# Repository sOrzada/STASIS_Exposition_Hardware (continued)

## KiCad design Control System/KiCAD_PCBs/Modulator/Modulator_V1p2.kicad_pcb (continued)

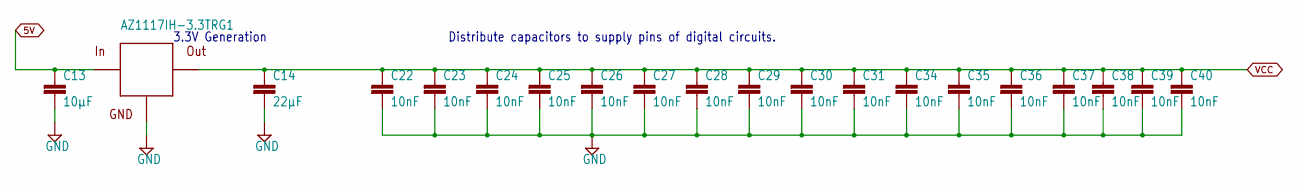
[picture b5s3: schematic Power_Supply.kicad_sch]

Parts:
C13: 10µF; C1206
C14: 22µF; C1206
C22, C23, C24, C25, C26, C27, C28, C29, C30, C31, C34, C35, C36, C37, C38, C39, C40: 10nF; C0603
U$9: AZ1117IH-3.3TRG1; SOT223

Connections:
5V: C13.1, U$9.3 (IN); also elsewhere on the board
GND: C13.2, C14.2, C22.2, C23.2, C24.2, C25.2, C26.2, C27.2, C28.2, C29.2, C30.2, C31.2, C34.2, C35.2, C36.2, C37.2, C38.2, C39.2, C40.2, U$9.1 (GND); also elsewhere on the board
VCC: C14.1, C22.1, C23.1, C24.1, C25.1, C26.1, C27.1, C28.1, C29.1, C30.1, C31.1, C34.1, C35.1, C36.1, C37.1, C38.1, C39.1, C40.1, U$9.2 (OUT), U$9.4 (OUT); also elsewhere on the board

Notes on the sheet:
Distribute capacitors to supply pins of digital circuits.
3.3V Generation

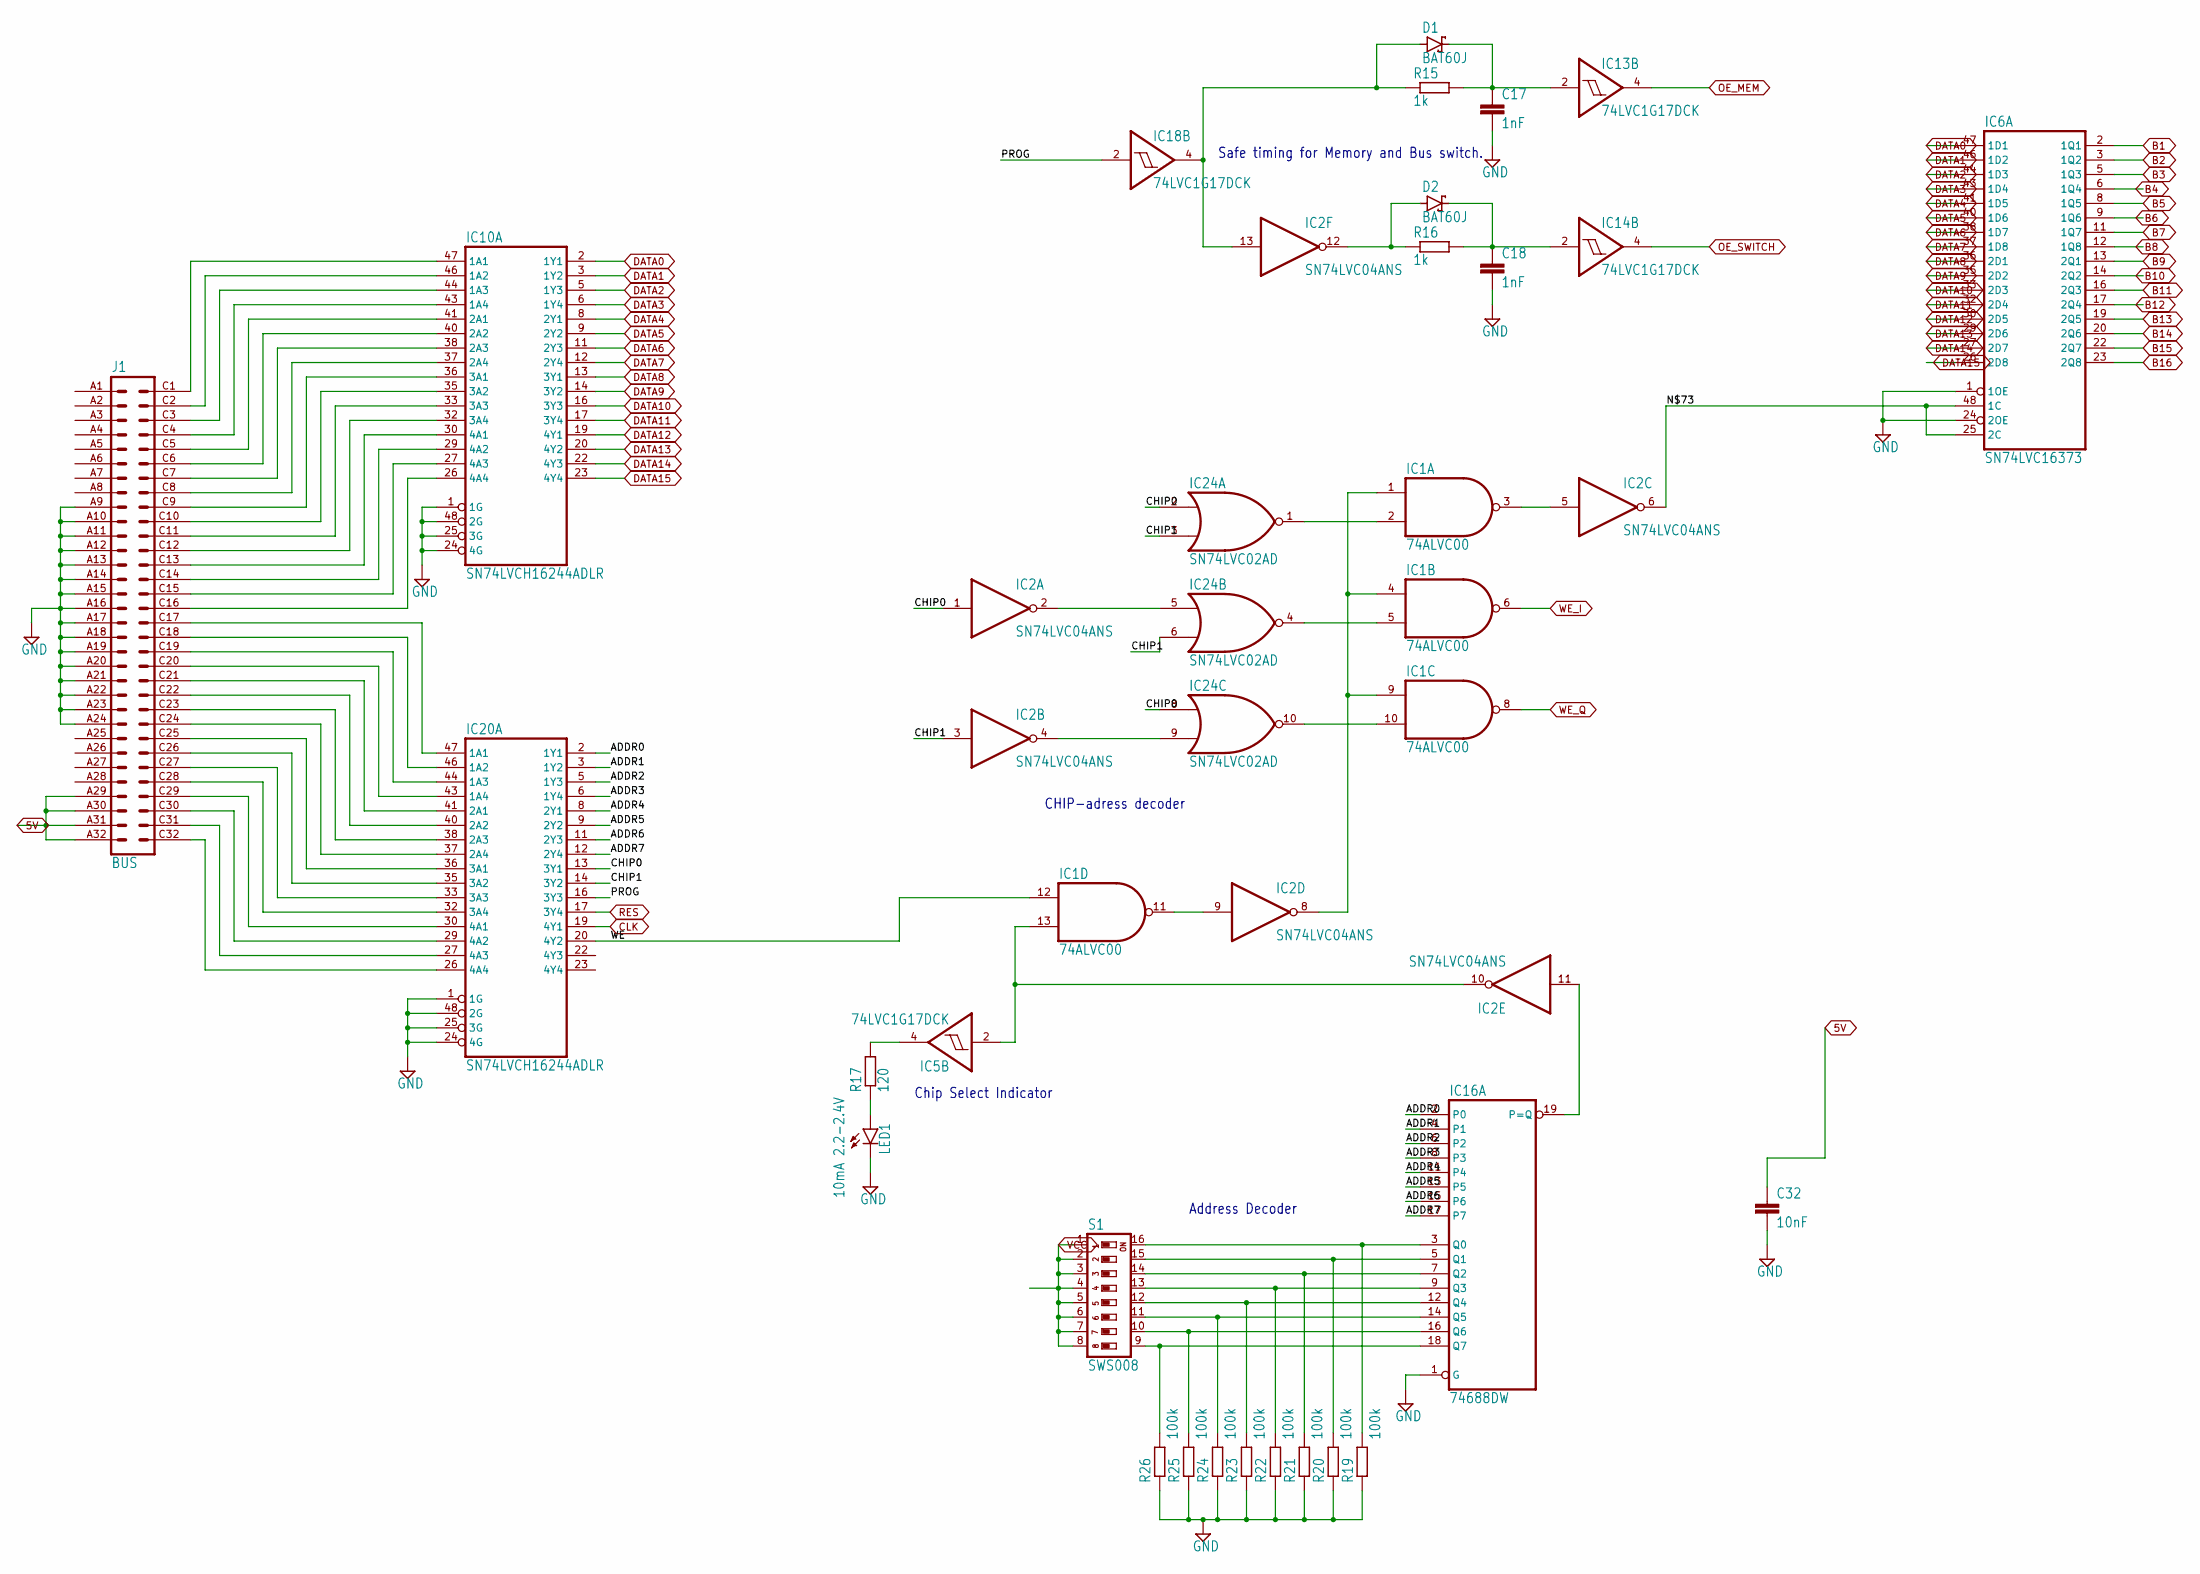
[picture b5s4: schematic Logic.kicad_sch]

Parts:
C17, C18: 1nF; C0805
C32: 10nF; C0603
D1, D2: BAT60J; SOD323_ST
IC1: 74ALVC00; SO14
IC2: SN74LVC04ANS; SO14
IC5, IC13, IC14, IC18: 74LVC1G17DCK; SC70-5
IC6: SN74LVC16373; SSOP48DL
IC10, IC20: SN74LVCH16244ADLR; SSOP48DL
IC16: 74688DW; SO20W
IC24: SN74LVC02AD; SO14
J1: BUS; VG64B
LED1: 10mA 2.2-2.4V; LED3MM
R15, R16: 1k; R0603
R17: 120; R0603
R19, R20, R21, R22, R23, R24, R25, R26: 100k; R0603
S1: SWS008; SMS-008

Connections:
5V: C32.1, J1.A29, J1.A30, J1.A31, J1.A32; also elsewhere on the board
ADDR0: IC16.2 (P0), IC20.2 (1Y1)
ADDR1: IC16.4 (P1), IC20.3 (1Y2)
ADDR2: IC16.6 (P2), IC20.5 (1Y3)
ADDR3: IC16.8 (P3), IC20.6 (1Y4)
ADDR4: IC16.11 (P4), IC20.8 (2Y1)
ADDR5: IC16.13 (P5), IC20.9 (2Y2)
ADDR6: IC16.15 (P6), IC20.11 (2Y3)
ADDR7: IC16.17 (P7), IC20.12 (2Y4)
B1: IC6.2 (1Q1); also elsewhere on the board
B2: IC6.3 (1Q2); also elsewhere on the board
B3: IC6.5 (1Q3); also elsewhere on the board
B4: IC6.6 (1Q4); also elsewhere on the board
B5: IC6.8 (1Q5); also elsewhere on the board
B6: IC6.9 (1Q6); also elsewhere on the board
B7: IC6.11 (1Q7); also elsewhere on the board
B8: IC6.12 (1Q8); also elsewhere on the board
B9: IC6.13 (2Q1); also elsewhere on the board
B10: IC6.14 (2Q2); also elsewhere on the board
B11: IC6.16 (2Q3); also elsewhere on the board
B12: IC6.17 (2Q4); also elsewhere on the board
B13: IC6.19 (2Q5); also elsewhere on the board
B14: IC6.20 (2Q6); also elsewhere on the board
B15: IC6.22 (2Q7); also elsewhere on the board
B16: IC6.23 (2Q8); also elsewhere on the board
CHIP0: IC2.1 (I), IC20.13 (3Y1), IC24.2 (I0), IC24.8 (I0)
CHIP1: IC2.3 (I), IC20.14 (3Y2), IC24.3 (I1), IC24.6 (I1)
CLK: IC20.19 (4Y1); also elsewhere on the board
DATA0: IC6.47 (1D1), IC10.2 (1Y1); also elsewhere on the board
DATA1: IC6.46 (1D2), IC10.3 (1Y2); also elsewhere on the board
DATA2: IC6.44 (1D3), IC10.5 (1Y3); also elsewhere on the board
DATA3: IC6.43 (1D4), IC10.6 (1Y4); also elsewhere on the board
DATA4: IC6.41 (1D5), IC10.8 (2Y1); also elsewhere on the board
DATA5: IC6.40 (1D6), IC10.9 (2Y2); also elsewhere on the board
DATA6: IC6.38 (1D7), IC10.11 (2Y3); also elsewhere on the board
DATA7: IC6.37 (1D8), IC10.12 (2Y4); also elsewhere on the board
DATA8: IC6.36 (2D1), IC10.13 (3Y1); also elsewhere on the board
DATA9: IC6.35 (2D2), IC10.14 (3Y2); also elsewhere on the board
DATA10: IC6.33 (2D3), IC10.16 (3Y3); also elsewhere on the board
DATA11: IC6.32 (2D4), IC10.17 (3Y4); also elsewhere on the board
DATA12: IC6.30 (2D5), IC10.19 (4Y1); also elsewhere on the board
DATA13: IC6.29 (2D6), IC10.20 (4Y2); also elsewhere on the board
DATA14: IC6.27 (2D7), IC10.22 (4Y3); also elsewhere on the board
DATA15: IC6.26 (2D8), IC10.23 (4Y4); also elsewhere on the board
GND: C17.2, C18.2, C32.2, IC1.7 (GND), IC2.7 (GND), IC5.3 (GND), IC6.1 (1OE), IC6.4 (GND@1), IC6.10 (GND@2), IC6.15 (GND@3), IC6.21 (GND@4), IC6.24 (2OE), IC6.28 (GND@5), IC6.34 (GND@6), IC6.39 (GND@7), IC6.45 (GND@8), IC10.1 (1G), IC10.4 (GND@1), IC10.10 (GND@2), IC10.15 (GND@3), IC10.21 (GND@4), IC10.24 (4G), IC10.25 (3G), IC10.28 (GND@5), IC10.34 (GND@6), IC10.39 (GND@7), IC10.45 (GND@8), IC10.48 (2G), IC13.3 (GND), IC14.3 (GND), IC16.1 (G), IC16.10 (GND), IC18.3 (GND), IC20.1 (1G), IC20.4 (GND@1), IC20.10 (GND@2), IC20.15 (GND@3), IC20.21 (GND@4), IC20.24 (4G), IC20.25 (3G), IC20.28 (GND@5), IC20.34 (GND@6), IC20.39 (GND@7), IC20.45 (GND@8), IC20.48 (2G), IC24.7 (GND), J1.A9, J1.A10, J1.A11, J1.A12, J1.A13, J1.A14, J1.A15, J1.A16, J1.A17, J1.A18, J1.A19, J1.A20, J1.A21, J1.A22, J1.A23, J1.A24, LED1.K (C), R19.1, R20.1, R21.1, R22.1, R23.1, R24.1, R25.1, R26.1; also elsewhere on the board
unnamed: IC10.47 (1A1), J1.C1
unnamed: IC10.46 (1A2), J1.C2
unnamed: C17.1, D1.C, IC13.2 (I), R15.2
unnamed: IC10.44 (1A3), J1.C3
unnamed: IC10.43 (1A4), J1.C4
unnamed: IC10.41 (2A1), J1.C5
unnamed: IC10.40 (2A2), J1.C6
unnamed: IC10.38 (2A3), J1.C7
unnamed: IC10.37 (2A4), J1.C8
unnamed: IC10.36 (3A1), J1.C9
unnamed: IC10.35 (3A2), J1.C10
unnamed: IC10.33 (3A3), J1.C11
unnamed: IC10.32 (3A4), J1.C12
unnamed: IC10.30 (4A1), J1.C13
unnamed: IC10.29 (4A2), J1.C14
unnamed: IC10.27 (4A3), J1.C15
unnamed: IC10.26 (4A4), J1.C16
unnamed: IC20.47 (1A1), J1.C17
unnamed: IC20.46 (1A2), J1.C18
unnamed: IC20.44 (1A3), J1.C19
unnamed: IC20.43 (1A4), J1.C20
unnamed: IC20.41 (2A1), J1.C21
unnamed: IC20.40 (2A2), J1.C22
unnamed: IC20.38 (2A3), J1.C23
unnamed: IC20.37 (2A4), J1.C24
unnamed: IC20.36 (3A1), J1.C25
unnamed: IC20.35 (3A2), J1.C26
unnamed: IC20.33 (3A3), J1.C27
unnamed: IC16.3 (Q0), R19.2, S1.16
unnamed: C18.1, D2.C, IC14.2 (I), R16.2
unnamed: D2.A, IC2.12 (O), R16.1
unnamed: IC16.5 (Q1), R20.2, S1.15
unnamed: IC16.7 (Q2), R21.2, S1.14
unnamed: IC16.9 (Q3), R22.2, S1.13
unnamed: IC16.12 (Q4), R23.2, S1.12
unnamed: IC16.14 (Q5), R24.2, S1.11
unnamed: IC16.16 (Q6), R25.2, S1.10
unnamed: IC16.18 (Q7), R26.2, S1.9
unnamed: IC1.2 (I1), IC24.1 (O)
unnamed: IC1.5 (I1), IC24.4 (O)
unnamed: IC2.6 (O), IC6.25 (2C), IC6.48 (1C)
unnamed: D1.A, IC2.13 (I), IC18.4 (O), R15.1
unnamed: IC2.2 (O), IC24.5 (I0)
unnamed: IC2.4 (O), IC24.9 (I1)
unnamed: IC20.32 (3A4), J1.C28
unnamed: IC1.10 (I1), IC24.10 (O)
unnamed: IC1.3 (O), IC2.5 (I)
unnamed: IC2.11 (I), IC16.19 (P=Q)
unnamed: IC1.13 (I1), IC2.10 (O), IC5.2 (I)
unnamed: IC1.1 (I0), IC1.4 (I0), IC1.9 (I0), IC2.8 (O)
unnamed: IC1.11 (O), IC2.9 (I)
unnamed: IC20.30 (4A1), J1.C29
unnamed: IC20.29 (4A2), J1.C30
unnamed: IC20.27 (4A3), J1.C31
unnamed: IC20.26 (4A4), J1.C32
unnamed: LED1.A, R17.1
unnamed: IC5.4 (O), R17.2
OE_MEM: IC13.4 (O); also elsewhere on the board
OE_SWITCH: IC14.4 (O); also elsewhere on the board
PROG: IC18.2 (I), IC20.16 (3Y3)
RES: IC20.17 (3Y4); also elsewhere on the board
VCC: IC1.14 (VCC), IC2.14 (VCC), IC5.5 (VCC), IC6.7 (VCC@1), IC6.18 (VCC@2), IC6.31 (VCC@3), IC6.42 (VCC@4), IC10.7 (VCC@1), IC10.18 (VCC@2), IC10.31 (VCC@3), IC10.42 (VCC@4), IC13.5 (VCC), IC14.5 (VCC), IC16.20 (VCC), IC18.5 (VCC), IC20.7 (VCC@1), IC20.18 (VCC@2), IC20.31 (VCC@3), IC20.42 (VCC@4), IC24.14 (VCC), S1.1, S1.2, S1.3, S1.4, S1.5, S1.6, S1.7, S1.8; also elsewhere on the board
WE: IC1.12 (I0), IC20.20 (4Y2)
WE_I: IC1.6 (O); also elsewhere on the board
WE_Q: IC1.8 (O); also elsewhere on the board

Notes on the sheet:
Address Decoder
Chip Select Indicator
Safe timing for Memory and Bus switch.
CHIP-adress decoder

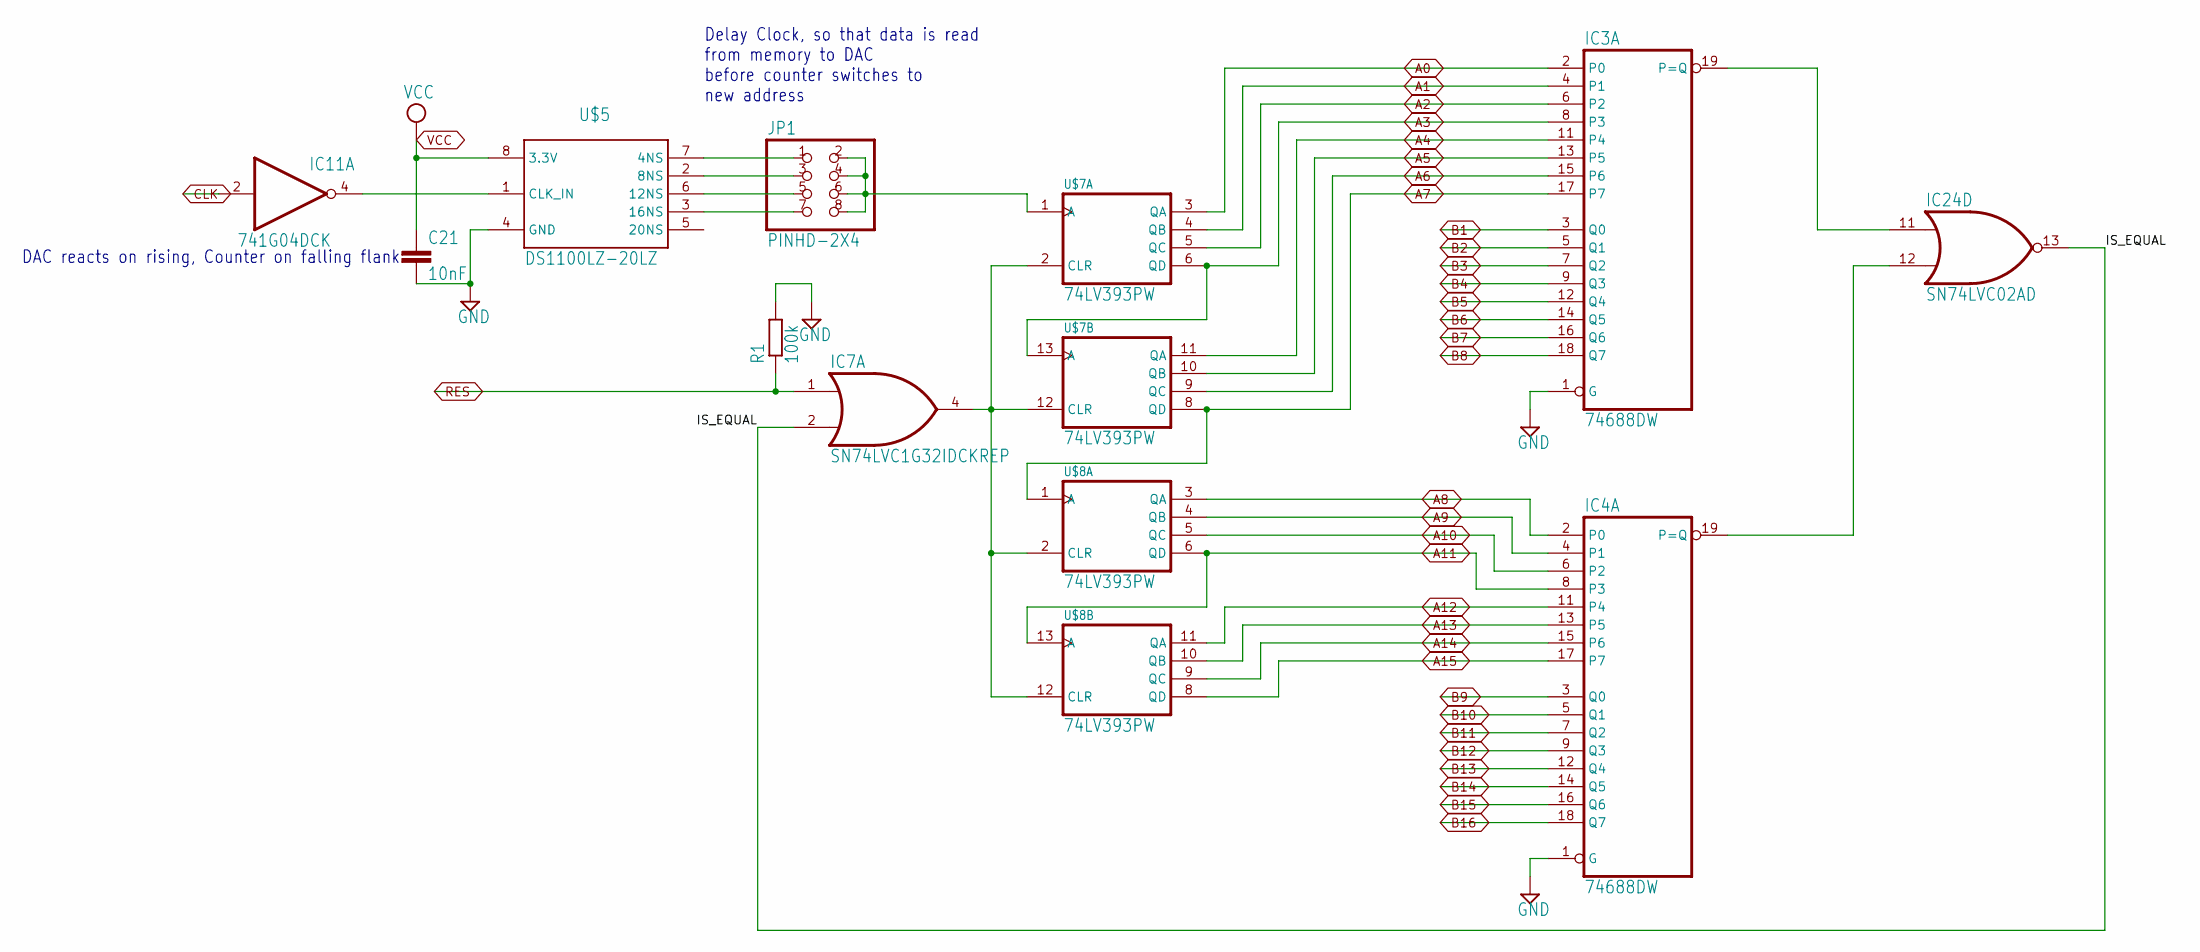
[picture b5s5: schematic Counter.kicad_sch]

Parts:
C21: 10nF; C0603
IC3, IC4: 74688DW; SO20W
IC7: SN74LVC1G32IDCKREP; SC70-5
IC11: 741G04DCK; SC70-5
IC24: SN74LVC02AD; SO14
JP1: PINHD-2X4; 2X04
R1: 100k; R0603
U$5: DS1100LZ-20LZ; SO-08
U$7, U$8: 74LV393PW; TSSOP14

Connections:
A0: IC3.2 (P0), U$7.3 (QA); also elsewhere on the board
A1: IC3.4 (P1), U$7.4 (QB); also elsewhere on the board
A2: IC3.6 (P2), U$7.5 (QC); also elsewhere on the board
A3: IC3.8 (P3), U$7.6 (QD), U$7.13 (A); also elsewhere on the board
A4: IC3.11 (P4), U$7.11 (QA); also elsewhere on the board
A5: IC3.13 (P5), U$7.10 (QB); also elsewhere on the board
A6: IC3.15 (P6), U$7.9 (QC); also elsewhere on the board
A7: IC3.17 (P7), U$7.8 (QD), U$8.1 (A); also elsewhere on the board
A8: IC4.2 (P0), U$8.3 (QA); also elsewhere on the board
A9: IC4.4 (P1), U$8.4 (QB); also elsewhere on the board
A10: IC4.6 (P2), U$8.5 (QC); also elsewhere on the board
A11: IC4.8 (P3), U$8.6 (QD), U$8.13 (A); also elsewhere on the board
A12: IC4.11 (P4), U$8.11 (QA); also elsewhere on the board
A13: IC4.13 (P5), U$8.10 (QB); also elsewhere on the board
A14: IC4.15 (P6), U$8.9 (QC); also elsewhere on the board
A15: IC4.17 (P7), U$8.8 (QD); also elsewhere on the board
B1: IC3.3 (Q0); also elsewhere on the board
B2: IC3.5 (Q1); also elsewhere on the board
B3: IC3.7 (Q2); also elsewhere on the board
B4: IC3.9 (Q3); also elsewhere on the board
B5: IC3.12 (Q4); also elsewhere on the board
B6: IC3.14 (Q5); also elsewhere on the board
B7: IC3.16 (Q6); also elsewhere on the board
B8: IC3.18 (Q7); also elsewhere on the board
B9: IC4.3 (Q0); also elsewhere on the board
B10: IC4.5 (Q1); also elsewhere on the board
B11: IC4.7 (Q2); also elsewhere on the board
B12: IC4.9 (Q3); also elsewhere on the board
B13: IC4.12 (Q4); also elsewhere on the board
B14: IC4.14 (Q5); also elsewhere on the board
B15: IC4.16 (Q6); also elsewhere on the board
B16: IC4.18 (Q7); also elsewhere on the board
CLK: IC11.2 (I); also elsewhere on the board
CLR: IC7.4 (O), U$7.2 (CLR), U$7.12 (CLR), U$8.2 (CLR), U$8.12 (CLR)
GND: C21.2, IC3.1 (G), IC3.10 (GND), IC4.1 (G), IC4.10 (GND), IC7.3 (GND), IC11.3 (GND), IC24.7 (GND), R1.2, U$5.4 (GND), U$7.7 (GND), U$8.7 (GND); also elsewhere on the board
IS_EQUAL: IC7.2 (I1), IC24.13 (O)
unnamed: IC3.19 (P=Q), IC24.11 (I0)
unnamed: IC4.19 (P=Q), IC24.12 (I1)
unnamed: JP1.2, JP1.4, JP1.6, JP1.8, U$7.1 (A)
unnamed: IC11.4 (O), U$5.1 (CLK_IN)
unnamed: JP1.1, U$5.7 (4NS)
unnamed: JP1.3, U$5.2 (8NS)
unnamed: JP1.5, U$5.6 (12NS)
unnamed: JP1.7, U$5.3 (16NS)
RES: IC7.1 (I0), R1.1; also elsewhere on the board
VCC: C21.1, IC3.20 (VCC), IC4.20 (VCC), IC7.5 (VCC), IC11.5 (VCC), IC24.14 (VCC), U$5.8 (3.3V), U$7.14 (VCC), U$8.14 (VCC); also elsewhere on the board

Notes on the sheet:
DAC reacts on rising, Counter on falling flank
Delay Clock, so that data is read from memory to DAC before counter switches to new address

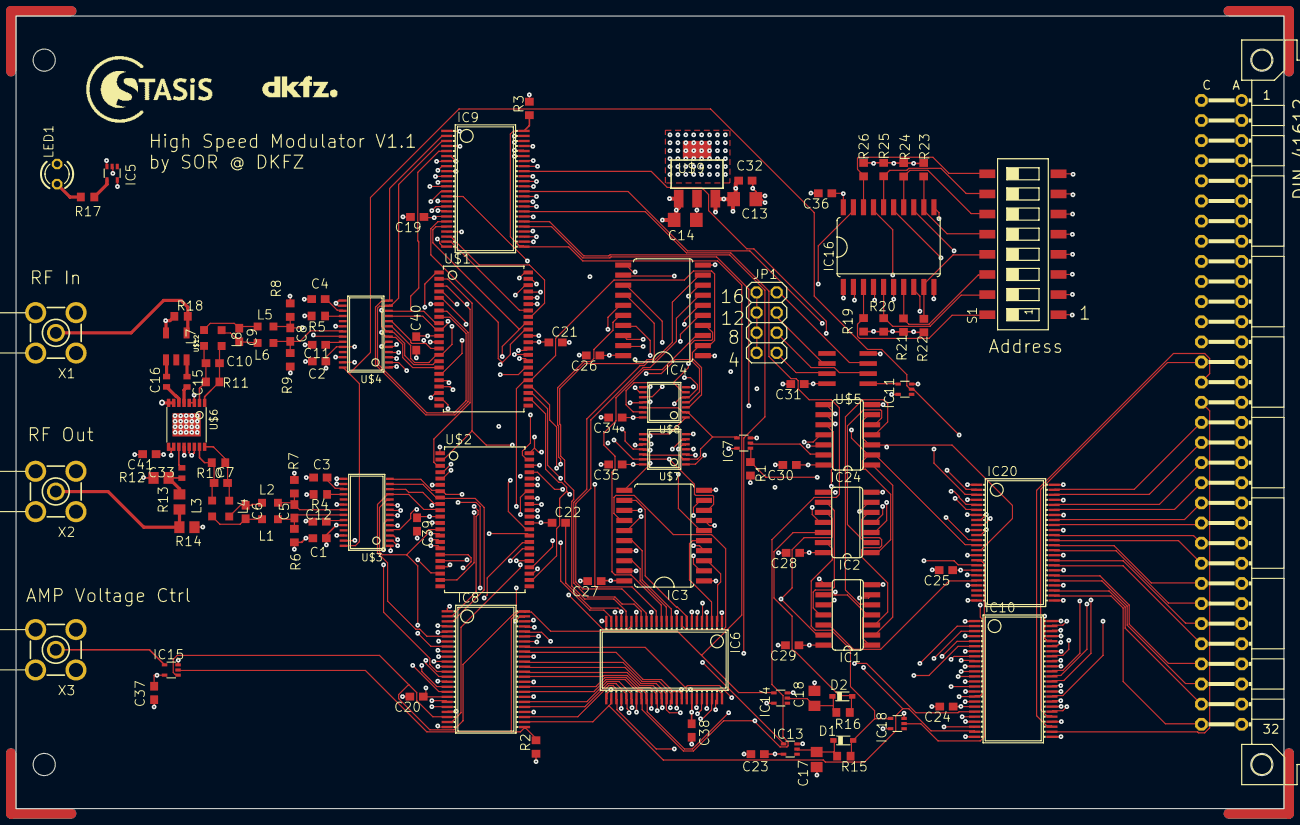
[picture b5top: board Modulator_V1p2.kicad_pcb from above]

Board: 6 copper layers, 160.0 x 100.0 mm, 114 parts (0 on the bottom side), 195 nets.

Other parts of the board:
U$10: LOGO_DKFZ
U$11: LOGO_STASIS

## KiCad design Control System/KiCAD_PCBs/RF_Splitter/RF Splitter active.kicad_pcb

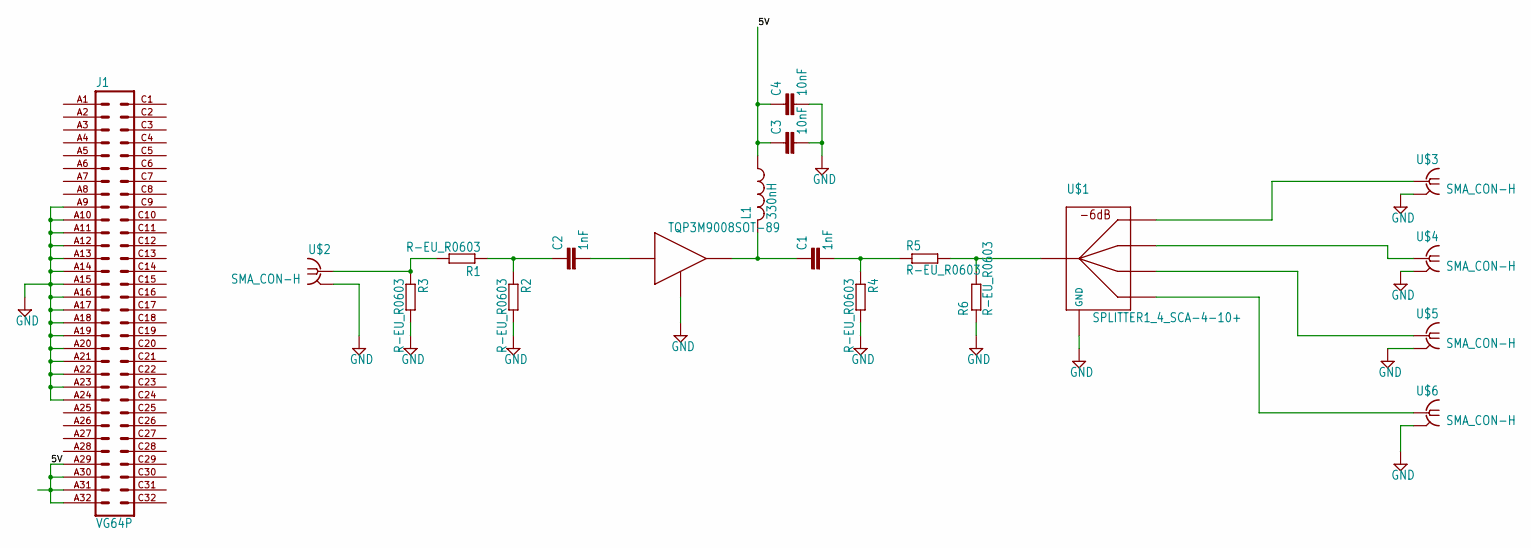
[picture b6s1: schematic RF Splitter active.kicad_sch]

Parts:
C1, C2: 1nF; C0603
C3, C4: 10nF; C0603
J1: VG64P
L1: 330nH; L2012C
R1, R2, R3, R4, R5, R6: R-EU_R0603; R0603
U$1: SPLITTER1_4_SCA-4-10+; SCA-4-10+
U$2, U$3, U$4, U$5, U$6: SMA_CON-H; BU-SMA-H
U$7: TQP3M9008SOT-89; SOT89

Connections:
5V: C3.1, C4.1, J1.A29, J1.A30, J1.A31, J1.A32, L1.1
GND: C3.2, C4.2, J1.A9, J1.A10, J1.A11, J1.A12, J1.A13, J1.A14, J1.A15, J1.A16, J1.A17, J1.A18, J1.A19, J1.A20, J1.A21, J1.A22, J1.A23, J1.A24, R2.2, R3.2, R4.2, R6.1, U$1.P$1 (GND), U$1.P$2 (GND), U$1.P$4 (GND), U$1.P$5 (GND), U$1.P$8 (GND), U$2.2 (GND@1), U$2.3 (GND@1), U$2.4 (GND@1), U$2.5 (GND@1), U$3.2 (GND@1), U$3.3 (GND@1), U$3.4 (GND@1), U$3.5 (GND@1), U$4.2 (GND@1), U$4.3 (GND@1), U$4.4 (GND@1), U$4.5 (GND@1), U$5.2 (GND@1), U$5.3 (GND@1), U$5.4 (GND@1), U$5.5 (GND@1), U$6.2 (GND@1), U$6.3 (GND@1), U$6.4 (GND@1), U$6.5 (GND@1), U$7.2 (GND), U$7.2@1 (GND)
unnamed: C2.2, U$7.1 (IN)
unnamed: U$1.P$6, U$3.1
unnamed: U$1.P$7, U$4.1
unnamed: U$1.P$9, U$5.1
unnamed: U$1.P$10, U$6.1
unnamed: C1.1, L1.2, U$7.3 (OUT)
unnamed: C1.2, R4.1, R5.1
unnamed: R5.2, R6.2, U$1.P$3
unnamed: R1.2, R3.1, U$2.1
unnamed: C2.1, R1.1, R2.1

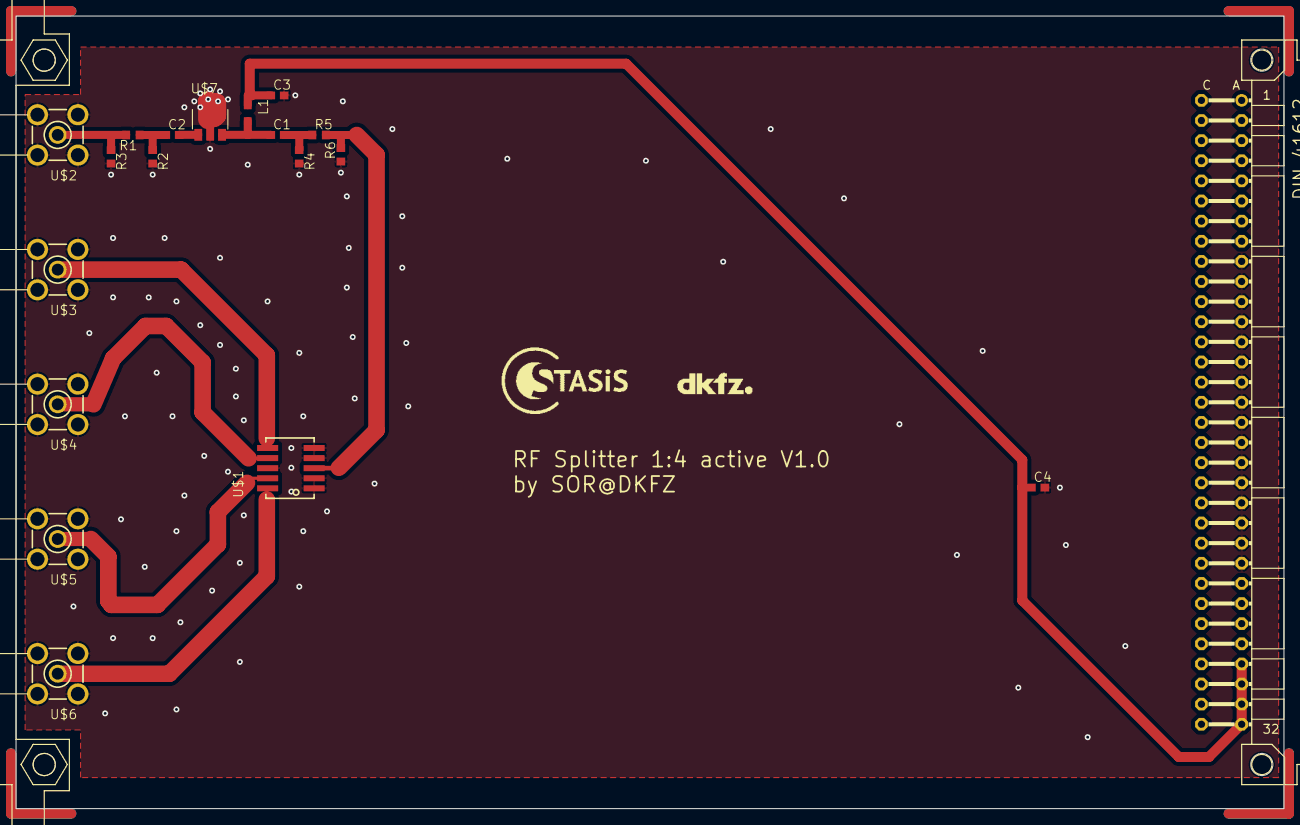
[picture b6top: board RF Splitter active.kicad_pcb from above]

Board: 2 copper layers, 160.0 x 100.0 mm, 21 parts (0 on the bottom side), 12 nets.

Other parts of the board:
U$8: LOGO_STASIS
U$9: LOGO_DKFZ
